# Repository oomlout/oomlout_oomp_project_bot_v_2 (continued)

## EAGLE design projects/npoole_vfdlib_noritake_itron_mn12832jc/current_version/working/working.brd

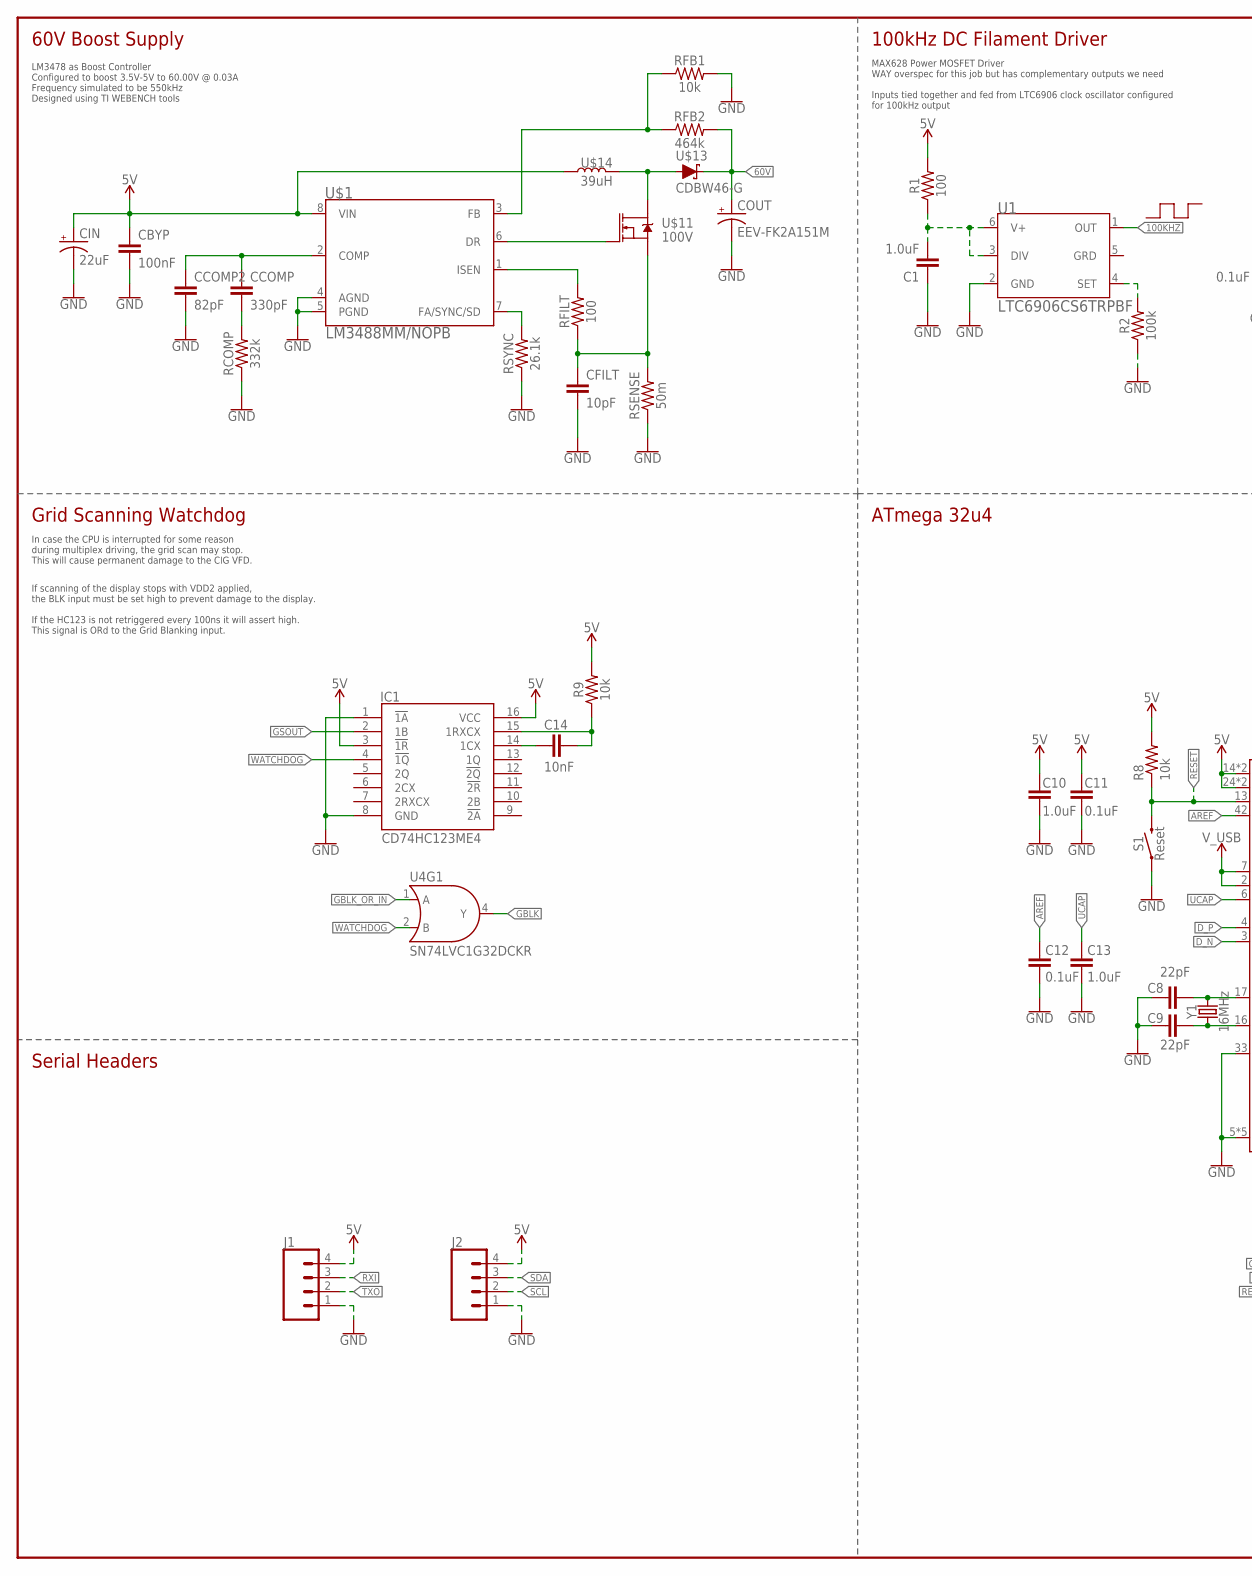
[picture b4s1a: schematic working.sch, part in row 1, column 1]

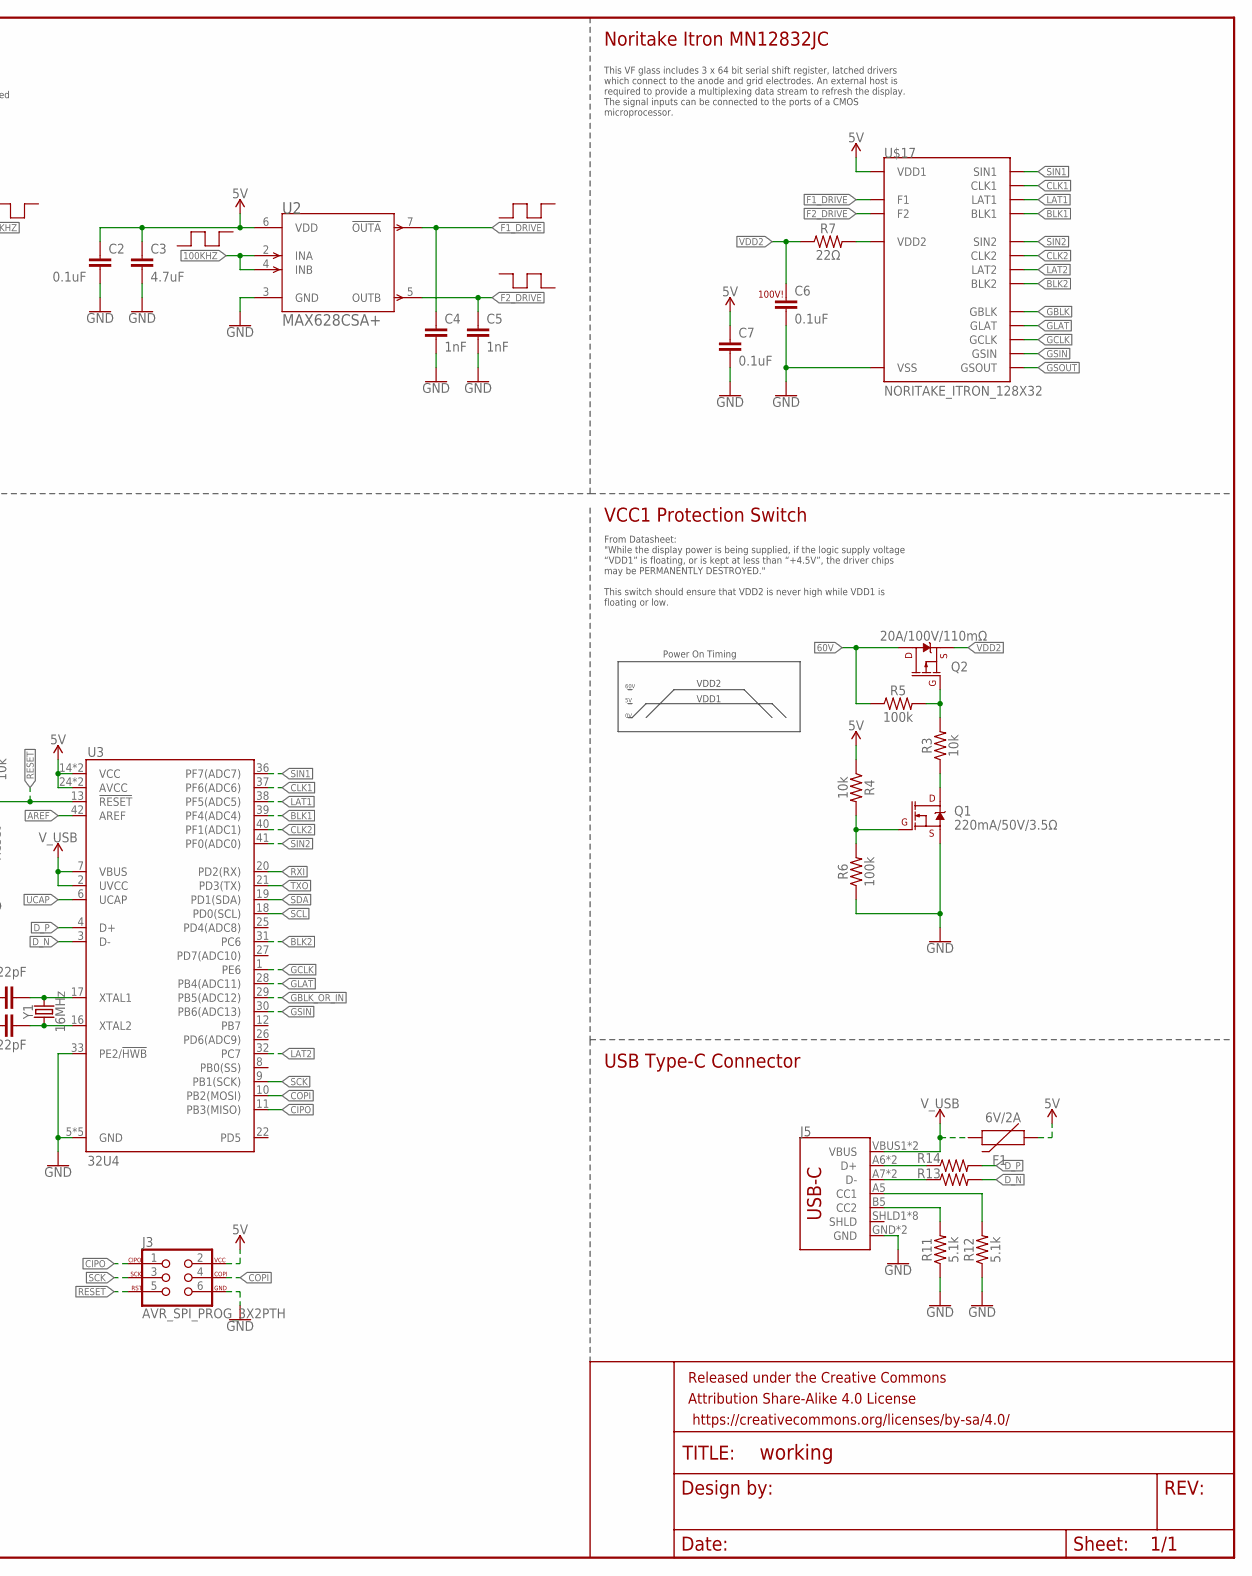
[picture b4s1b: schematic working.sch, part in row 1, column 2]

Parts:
C1, C10, C13: 1.0uF; 0603
C2, C6, C7, C11, C12: 0.1uF; 0603
C3: 4.7uF; 0603
C4, C5: 1nF; 0603
C8, C9: 22pF; 0603
C14: 10nF; 0603
CBYP: 100nF; 0805
CCOMP: 330pF; 0805
CCOMP2: 82pF; 0805
CFILT: 10pF; 0603
CIN: 22uF; SM_RADIAL_C
COUT: EEV-FK2A151M; SM_RADIAL_J16
F1: 6V/2A; 1210
FRAME1: FRAME-LEDGERNO_FOOTPRINT; DUMMY
IC1: CD74HC123ME4; SOIC127P600X175-16N
J1, J2: CONN_041X04_NO_SILK; 1X04_NO_SILK
J3: AVR_SPI_PROG_3X2PTH; 2X3
J5: USB_C5; USB-C-16P-5
Q1: 220mA/50V/3.5Ω; SOT23-3
Q2: 20A/100V/110mΩ; TO-252/DPAK
R1: 100; 0603
R2, R5, R6: 100k; 0603
R3, R4, R8, R9: 10k; 0603
R7, R13, R14: 22Ω; 0603
R11, R12: 5.1k; 0603
RCOMP: 332k; 0603
RFB1: 10k; 0603
RFB2: 464k; 0603
RFILT: 100; 0603
RSENSE: 50m; 0603
RSYNC: 26.1k; 0603
S1: Reset; TACTILE_SWITCH_SMD_4.6X2.8MM
U1: LTC6906CS6TRPBF; TSOT-23_6_ADI
U2: MAX628CSA+; 21-0041B_8_MXM
U3: 32U4; TQFP44
U4: SN74LVC1G32DCKR; SOT353
U$1: LM3488MM/NOPB; MUA08A
U$11: 100V; PG-TDSON-8
U$13: CDBW46-G; SOD-123
U$14: 39uH; IND_NPI54C
U$17: NORITAKE_ITRON_128X32
Y1: 16MHz; CRYSTAL-SMD-5X3.2-4PAD

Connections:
5V: C2.1, C3.1, C7.1, C10.2, C11.2, CBYP.1, CIN.1 (+), F1.1, IC1.3 (!1R), IC1.16 (VCC), J1.4, J2.4, J3.2, R1.2, R4.1, R8.2, R9.2, U2.6 (VDD), U3.14 (VCC), U3.24 (AVCC), U3.34 (VCC), U3.44 (AVCC), U$1.8 (VIN), U$14.1, U$17.P$13 (VDD1)
60V: COUT.1 (+), Q2.2 (D), R5.1, RFB2.2, U$13.1 (C)
100KHZ: U1.1 (OUT), U2.2 (INA), U2.4 (INB)
AREF: C12.2, U3.42 (AREF)
BLK1: U3.39 (PF4(ADC4)), U$17.P$4 (BLK1)
BLK2: U3.31 (PC6), U$17.P$23 (BLK2)
CIPO: J3.1, U3.11 (PB3(MISO))
CLK1: U3.37 (PF6(ADC6)), U$17.P$6 (CLK1)
CLK2: U3.40 (PF1(ADC1)), U$17.P$21 (CLK2)
COPI: J3.4, U3.10 (PB2(MOSI))
D-_HV: J5.A7 (D-), J5.B7 (D-), R13.1
DP_HV: J5.A6 (D+), J5.B6 (D+), R14.1
D_N: R13.2, U3.3 (D-)
D_P: R14.2, U3.4 (D+)
F1_DRIVE: C4.1, U2.7 (!OUTA), U$17.P$1 (F1), U$17.P$2 (F1), U$17.P$3 (F1)
F2_DRIVE: C5.1, U2.5 (OUTB), U$17.P$26 (F2), U$17.P$27 (F2), U$17.P$28 (F2)
GBLK: U4.4 (Y), U$17.P$14 (GBLK)
GBLK_OR_IN: U3.29 (PB5(ADC12)), U4.1 (A)
GCLK: U3.1 (PE6), U$17.P$16 (GCLK)
GLAT: U3.28 (PB4(ADC11)), U$17.P$15 (GLAT)
GND: C1.1, C2.2, C3.2, C4.2, C5.2, C6.2, C7.2, C8.2, C9.2, C10.1, C11.1, C12.1, C13.1, CBYP.2, CCOMP2.2, CFILT.2, CIN.2 (-), COUT.2 (-), IC1.1 (!1A), IC1.8 (GND), J1.1, J2.1, J3.6, J5.GND, J5.GND2 (GND), Q1.2 (S), R2.1, R6.1, R11.1, R12.1, RCOMP.1, RFB1.2, RSENSE.1, RSYNC.1, S1.1, S1.2 (1), U1.2 (GND), U2.3 (GND), U3.5 (GND), U3.15 (GND), U3.23 (GND), U3.33 (PE2/!HWB), U3.35 (GND), U3.43 (GND), U$1.4 (AGND), U$1.5 (PGND), U$17.P$11 (VSS), U$17.P$12 (VSS)
GSIN: U3.30 (PB6(ADC13)), U$17.P$17 (GSIN)
GSOUT: IC1.2 (1B), U$17.P$18 (GSOUT)
LAT1: U3.38 (PF5(ADC5)), U$17.P$5 (LAT1)
LAT2: U3.32 (PC7), U$17.P$22 (LAT2)
unnamed: RSYNC.2, U$1.7 (FA/SYNC/SD)
unnamed: CCOMP.1, CCOMP2.1, U$1.2 (COMP)
unnamed: RFILT.2, U$1.1 (ISEN)
unnamed: CCOMP.2, RCOMP.2
unnamed: CFILT.1, RFILT.1, RSENSE.2, U$11.1 (S), U$11.2 (S), U$11.3 (S)
unnamed: U$11.5 (D), U$11.6 (D), U$11.7 (D), U$11.8 (D), U$11.9 (D), U$13.2 (A), U$14.2
unnamed: RFB1.1, RFB2.1, U$1.3 (FB)
unnamed: U$1.6 (DR), U$11.4 (G)
unnamed: C1.2, R1.1, U1.3 (DIV), U1.6 (V+)
unnamed: R2.2, U1.4 (SET)
unnamed: R7.2, U$17.P$9 (VDD2), U$17.P$10 (VDD2)
unnamed: Q1.1 (G), R4.2, R6.2
unnamed: Q1.3 (D), R3.1
unnamed: Q2.1 (G), R3.2, R5.2
unnamed: C9.1, U3.16 (XTAL2), Y1.1
unnamed: C8.1, U3.17 (XTAL1), Y1.3 (2)
unnamed: C14.2, IC1.14 (1CX)
unnamed: C14.1, IC1.15 (1RXCX), R9.1
unnamed: J5.A5 (CC1), R12.2
unnamed: J5.B5 (CC2), R11.2
RESET: J3.5, R8.1, S1.3 (2), S1.4 (2), U3.13 (!RESET)
RXI: J1.3, U3.20 (PD2(RX))
SCK: J3.3, U3.9 (PB1(SCK))
SCL: J2.2, U3.18 (PD0(SCL))
SDA: J2.3, U3.19 (PD1(SDA))
SIN1: U3.36 (PF7(ADC7)), U$17.P$7 (SIN1)
SIN2: U3.41 (PF0(ADC0)), U$17.P$20 (SIN2)
TXO: J1.2, U3.21 (PD3(TX))
UCAP: C13.2, U3.6 (UCAP)
VDD2: C6.1, Q2.3 (S), R7.1
V_USB: F1.2, J5.VBUS1 (VBUS), J5.VBUS2 (VBUS), U3.2 (UVCC), U3.7 (VBUS)
WATCHDOG: IC1.4 (!1Q), U4.2 (B)

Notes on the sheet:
60V Boost Supply
100kHz DC Filament Driver
100V!
Noritake Itron MN12832JC
VCC1 Protection Switch
LM3478 as Boost Controller Configured to boost 3.5V-5V to 60.00V @ 0.03A Frequency simulated to be 550kHz Designed using TI WEBENCH tools
MAX628 Power MOSFET Driver WAY overspec for this job but has complementary outputs we need Inputs tied together and fed from LTC6906 clock oscillator configured for 100kHz output
From Datasheet: "While the display power is being supplied, if the logic supply voltage “VDD1” is floating, or is kept at less than “+4.5V”, the driver chips may be PERMANENTLY DESTROYED." This switch should ensure that VDD2 is never high while VDD1 is floating or low.
VDD1
VDD2
60V
Power On Timing
This VF glass includes 3 x 64 bit serial shift register, latched drivers which connect to the anode and grid electrodes. An external host is required to provide a multiplexing data stream to refresh the display. The signal inputs can be connected to the ports of a CMOS microprocessor.
ATmega 32u4
USB Type-C Connector
Grid Scanning Watchdog
In case the CPU is interrupted for some reason during multiplex driving, the grid scan may stop. This will cause permanent damage to the CIG VFD.
If scanning of the display stops with VDD2 applied, the BLK input must be set high to prevent damage to the display. If the HC123 is not retriggered every 100ns it will assert high. This signal is ORd to the Grid Blanking input.
Serial Headers

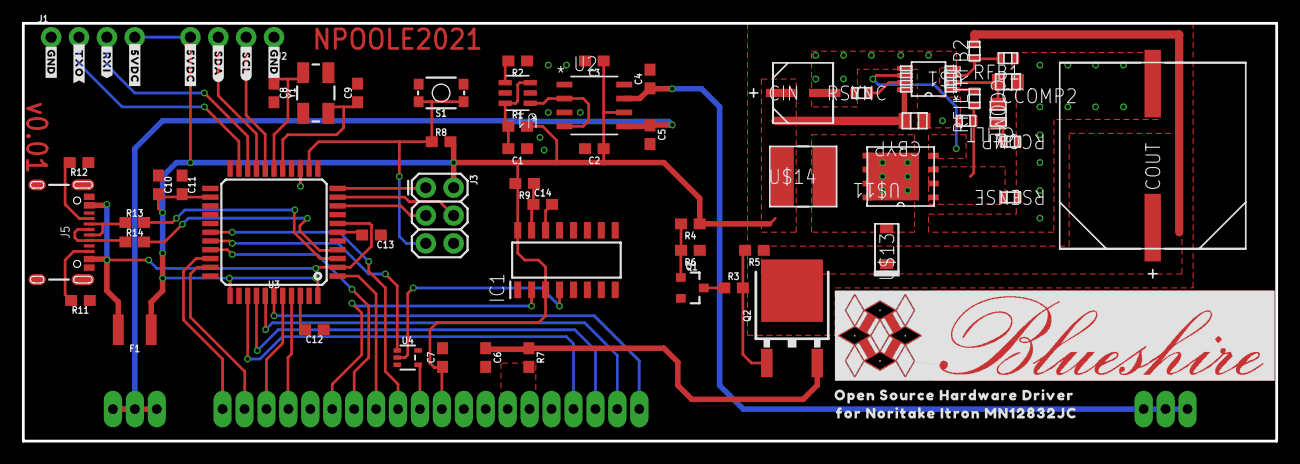
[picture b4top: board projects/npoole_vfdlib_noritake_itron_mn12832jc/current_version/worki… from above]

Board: 2 copper layers, 114.3 x 38.1 mm, 72 parts (1 on the bottom side), 57 nets.

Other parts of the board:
U$2: BLUESHIRE_COPPER#SVG1
U$3: BLUESHIRE_SILK#SVG0
U$4: BLUESHIRE_STOP#SVG2
U$5: OPEN_SOURCE_HARDWARE_DRIVER0
U$6: FOR_NORITAKE_ITRON_MN12832JC0
U$7, U$15: #GND#0
U$8: #_SCL#0
U$9: #_SDA#0
U$10, U$12: #_5VDC#0
U$16: #_RXI#0
U$18: #_TXO#0

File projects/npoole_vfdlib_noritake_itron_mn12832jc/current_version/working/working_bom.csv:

"Id";"Designator";"Footprint";"Quantity";"Designation";"Supplier and ref";
1;"U$18";"#_TXO#0";1;"";;;
2;"CCOMP0";"0805";1;"330pF";;;
3;"R7,R14,R13";"0603";3;"22Ω";;;
4;"F1";"1210";1;"6V/2A";;;
5;"C8,C9";"0603";2;"22pF";;;
6;"COUT0";"SM_RADIAL_J16";1;"EEV-FK2A151M";;;
7;"C12,C6,C7,C2,C11";"0603";5;"0.1uF";;;
8;"U$15,U$7";"#GND#0";2;"";;;
9;"U2";"21-0041B_8_MXM";1;"MAX628CSA+";;;
10;"C4,C5";"0603";2;"1nF";;;
11;"IC1";"SOIC127P600X175-16N";1;"CD74HC123ME4";;;
12;"J1,J2";"1X04_NO_SILK";2;"";;;
13;"U$3";"BLUESHIRE_SILK#SVG0";1;"";;;
14;"S1";"TACTILE_SWITCH_SMD_4.6X2.8MM";1;"Reset";;;
15;"U$16";"#_RXI#0";1;"";;;
16;"R6,R2,R5";"0603";3;"100k";;;
17;"U$10,U$12";"#_5VDC#0";2;"";;;
18;"U$8";"#_SCL#0";1;"";;;
19;"CCOMP2";"0805";1;"82pF";;;
20;"Q1";"SOT23-3";1;"220mA/50V/3.5Ω";;;
21;"CBYP0";"0805";1;"100nF";;;
22;"U$14";"IND_NPI54C";1;"39uH";;;
23;"R3,R8,RFB1,R9,R4";"0603";5;"10k";;;
24;"U$6";"FOR_NORITAKE_ITRON_MN12832JC0";1;"";;;
25;"J3";"2X3";1;"AVR_SPI_PROG_3X2PTH";;;
26;"C3";"0603";1;"4.7uF";;;
27;"RCOMP0";"0603";1;"332k";;;
28;"RFILT0,R1";"0603";2;"100";;;
29;"U$11";"PG-TDSON-8";1;"100V";;;
30;"FRAME1";"DUMMY";1;"FRAME-LEDGERNO_FOOTPRINT";;;
31;"U$5";"OPEN_SOURCE_HARDWARE_DRIVER0";1;"";;;
32;"U1";"TSOT-23_6_ADI";1;"LTC6906CS6TRPBF";;;
33;"Q2";"TO-252_DPAK";1;"20A/100V/110mΩ";;;
34;"RSYNC0";"0603";1;"26.1k";;;
35;"CFILT0";"0603";1;"10pF";;;
36;"Y1";"CRYSTAL-SMD-5X3.2-4PAD";1;"16MHz";;;
37;"U$4";"BLUESHIRE_STOP#SVG2";1;"";;;
38;"CIN0";"SM_RADIAL_C";1;"22uF";;;
39;"RSENSE0";"0603";1;"50m";;;
40;"U3";"TQFP44";1;"32U4";;;
41;"R11,R12";"0603";2;"5.1k";;;
42;"U4";"SOT353";1;"SN74LVC1G32DCKR";;;
43;"U$9";"#_SDA#0";1;"";;;
44;"U$13";"SOD-123";1;"CDBW46-G";;;
45;"C10,C13,C1";"0603";3;"1.0uF";;;
46;"C14";"0603";1;"10nF";;;
47;"RFB2";"0603";1;"464k";;;
48;"U$2";"BLUESHIRE_COPPER#SVG1";1;"";;;
49;"U$1";"MUA08A";1;"LM3488MM/NOPB";;;
50;"J5";"USB-C-16P-5";1;"";;;
51;"U$17";"NORITAKE_ITRON_128X32";1;"NORITAKE_ITRON_128X32";;;

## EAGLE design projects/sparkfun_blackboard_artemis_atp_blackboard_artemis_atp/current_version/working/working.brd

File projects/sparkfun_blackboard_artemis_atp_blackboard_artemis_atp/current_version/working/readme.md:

# blackboard_artemis_atp
 
## summary 
* id: sparkfun_blackboard_artemis_atp_blackboard_artemis_atp
* user: sparkfun
* name: blackboard_artemis_atp
* board: blackboard_artemis_atp
* repo: https://github.com/sparkfun/BlackBoard_Artemis_ATP

* src_file_repo_sch: 
* src_file_repo_sch_link: https://github.com/sparkfun/BlackBoard_Artemis_ATP/tree/master/
* full details link: https://github.com/oomlout/oomlout_oomp_project_bot_v_2/tree/main/projects/sparkfun_blackboard_artemis_atp_blackboard_artemis_atp/current_version/working

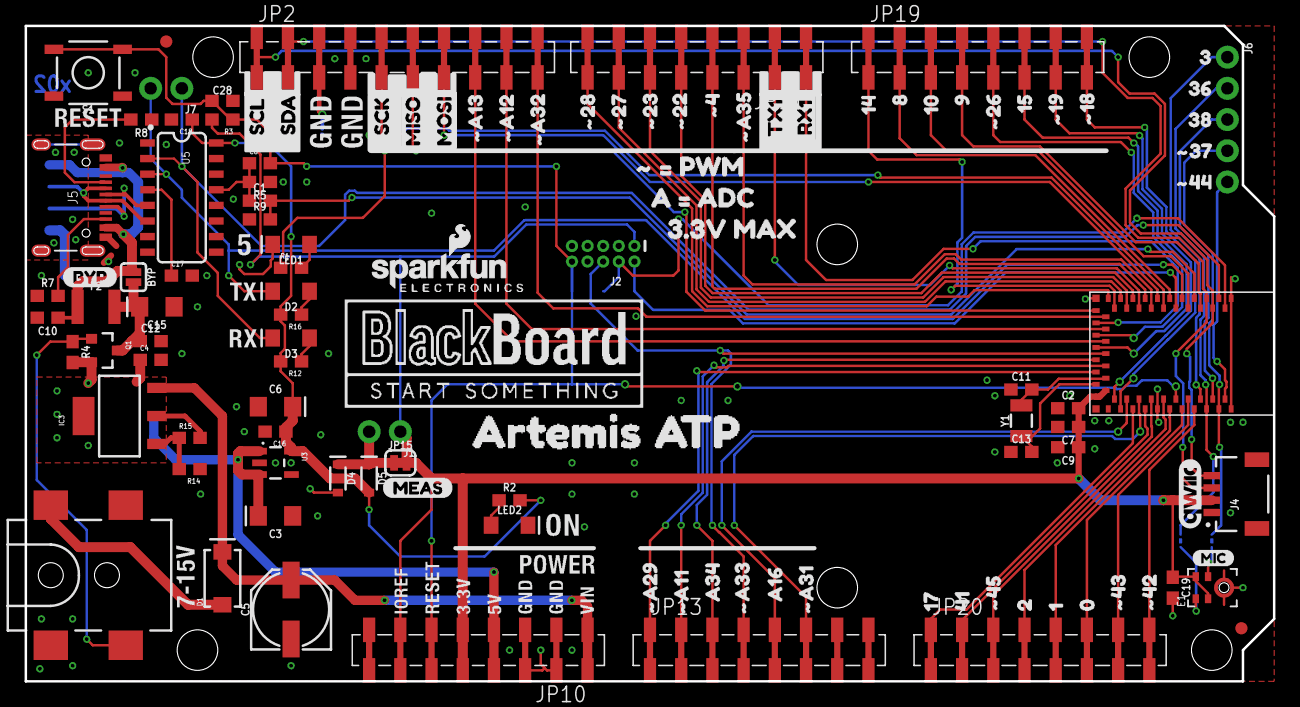
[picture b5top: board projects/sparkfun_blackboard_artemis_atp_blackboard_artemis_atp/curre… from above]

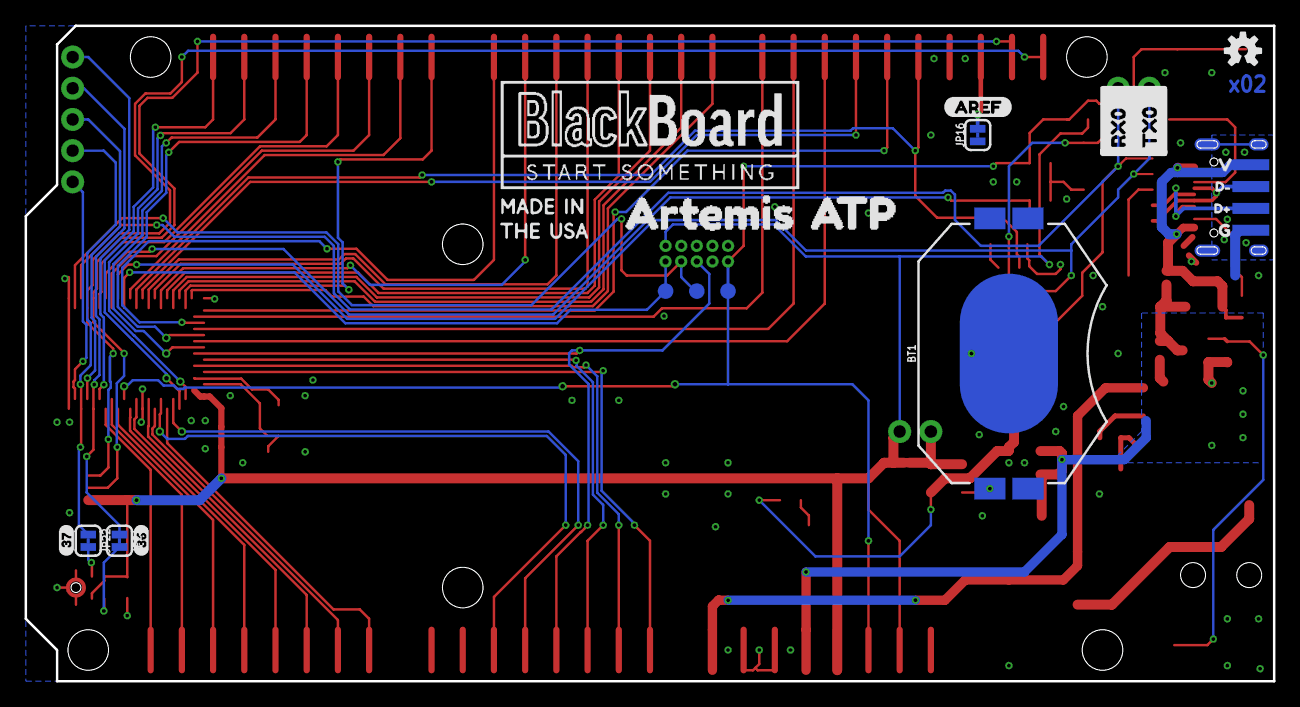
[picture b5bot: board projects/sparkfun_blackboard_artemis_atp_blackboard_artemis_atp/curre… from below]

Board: 2 copper layers, 101.6 x 53.3 mm, 149 parts (23 on the bottom side), 77 nets.

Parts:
BT1: CR2032; BATTCON_20MM_4LEGS_OVERPASTE
BYP: BYP; SMT-JUMPER_2_NO_SILK
C1: 2.2uF; 0603
C2, C4, C8, C10, C12, C18, C19: 0.1uF; 0603
C3, C6, C15: 10uF; EIA3216
C5: 47uF; PANASONIC_D
C7: 10uF; 0603
C9, C16: 1.0uF; 0603
C11, C13: 15pF; 0603
C17: 10nF; 0603
C28: 1nF; 0603
D1: 1A/40V/500mV; SMA-DIODE
D2: GREEN; LED-1206
D3: Yellow; LED-1206
D4, D5: 1A/23V/620mV; SOD-323
E1: SPH0641LM4H-1; SPH0641LM4H-1_MICROPHONE
F2: 6V/2A; 1210
FRAME1: FRAME-LETTER; CREATIVE_COMMONS
FRAME2: FRAME-LETTERNO_PACKAGE; DUMMY
IC3: LM1117; SOT223-ALT1
J1, J7: 1X02_NO_SILK
J2: CORTEX_DEBUG; 2X5-PTH-1.27MM-NO_SILK
J3: POWER_JACKTOE; POWER_JACK_SMD_OVERPASTE_TOE
J4: JST04_1MM_RA
J5: USB-C; USB-C-16P
J6: 1X05_NO_SILK
JP1: SFE_LOGO_NAME.1_INCH; SFE_LOGO_NAME_.1
JP2: M10SMD_COMBO; 1X10_SMD_COMBINED
JP3, JP4, JP5, JP6, JP17, JP18: STAND-OFF
JP7: SFE_LOGO_FLAME.1_INCH; SFE_LOGO_FLAME_.1
JP8, JP9: FIDUCIAL1X2; FIDUCIAL-1X2
JP10: 1X08_SMD_COMBINED
JP11, JP13, JP19, JP20: JP11; 1X08_SMD_COMBINED
JP14: USB_SOLDER_PADS; USB-SOLDER-PADS
JP15, JP16, JP21, JP22: SMT-JUMPER_2_NC_TRACE_SILK
LED1: BLUE; LED-1206
LED2: GREEN; LED-1206
Q1: 1.1A/60V/600mΩ; SOT23-3
R1, R12, R16: 4.7k; 0603
R2, R4, R9: 10k; 0603
R3, R5: 100k; 0603
R7, R8: 5.1k; 0603
R14: 715; 0603
R15: 240; 0603
S1: TACTILE_SWITCH_SMD_5.2MM
TP1, TP2, TP3: PAD.03X.05
U3: AP2112-3.3V; SOT23-5
U4: ARTEMIS_MODULESMD; ARTEMIS_FP
U5: CH340C; SO016
U$1, U$3: BLACKBOARDLOGO#PNG
U$2: D#3
U$4: MADEINUSA#PNG
U$9: QWIIC_COPYRIGHT_SMALL
U$10: D#4
U$11: G1
U$12: V0
U$13: #A332
U$14, U$15: ARTEMIS0
U$16: OSHW-LOGOS; OSHW-LOGO-S
U$17: A160
U$18: SCL1
U$19: #48
U$20: AREF2
U$21: #229
U$22: SDA0
U$23: #3711
U$24: #187
U$25: #2310
U$26: #2711
U$27: #2812
U$28, U$61: ATP1
U$29: #A113
U$30: #A294
U$31: #A310
U$32: #196
U$33: #A357
U$34: #A1214
U$35: #A1315
U$36: #A3213
U$37: #264
U$38: A342
U$39: #4213
U$40: #4314
U$41: #4412
U$42: #4518
U$43: 015
U$44: 38
U$45: 81
U$46: 93
U$47: MISO8
U$48: MOSI7
U$49: RX01
U$50: SCK9
U$51: 102
U$52: 116
U$53: TX00
U$54: 140
U$55: 155
U$56: 217
U$57: 369
U$58: 1720
U$59: 3810
U$60: 4119
U$62: MIC0
U$63: 364
U$64: 373
U$66: #_#_PWM7
U$67: 3#3V_MAX2
U$68: BYP0
U$69: A_#_ADC6
U$70: MEAS3
U$71: RX11
U$72: TX10
Y1: 32.768kHz; CRYSTAL-SMD-3.2X1.5MM

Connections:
3.3V: C6.+, C16.1, C18.1, D5.A, R2.2, R12.2, R16.2, U3.5, U5.16
5V: C3.+, C4.1, IC3.2, IC3.4, JP10.4A, JP10.4B, Q1.2, R4.2, R15.2, U3.1, U3.3
!DTR: C1.1, C8.1, R5.2, U5.13
!RESET: C8.2, C28.1, J2.10, JP10.6A, JP10.6B, R3.1, S1.3, S1.4, TP3.P$1, U4.~RST
AD16: JP13.5A, JP13.5B, U4.AD16
AD34: JP13.3A, JP13.3B, U4.AD34
BOOT: C1.2, R9.2, U4.BOOT
CC1: J5.A5, R8.2
CC2: J5.B5, R7.2
D0: JP20.6A, JP20.6B, U4.D0
D1: JP20.5A, JP20.5B, U4.D1
D2: JP20.4A, JP20.4B, U4.D2
D3: J6.1, U4.D3
D8: JP19.2A, JP19.2B, U4.D8
D9: JP19.4A, JP19.4B, U4.D9
D10: JP19.3A, JP19.3B, U4.D10
D14: JP19.1A, JP19.1B, U4.D14
D15: JP19.6A, JP19.6B, U4.D15
D17: JP20.1A, JP20.1B, U4.D17
D36: J6.2, JP21.1, U4.D36
D38: J6.3, U4.D38
D40/SDA: J4.3, JP2.2A, JP2.2B, U4.D40
D41: JP20.2A, JP20.2B, U4.D41
D+: J5.A6, J5.B6, JP14.D+, U5.5
D-: J5.A7, J5.B7, JP14.D-, U5.6
GND: BT1.2, C2.1, C3.-, C4.2, C5.-, C6.-, C7.2, C9.2, C10.2, C11.1, C12.2, C13.1, C15.-, C16.2, C17.2, C18.2, C19.2, C28.2, E1.3, E1.6, E1.7, E1.8, J2.3, J2.5, J2.9, J3.GND, J4.1, J5.GND, J5.GND2, JP2.4A, JP2.4B, JP10.2A, JP10.2B, JP10.3A, JP10.3B, JP14.GND, JP16.1, LED1.C, LED2.C, R5.1, R7.1, R8.1, R9.1, R14.1, S1.1, S1.2, U3.2, U4.GND@1, U4.GND@22, U4.GND@38, U4.GND@39, U4.GND@47, U4.GND@59, U5.1
INSERT: J3.P$4, Q1.1, R4.1
unnamed: LED1.A, R1.2
unnamed: LED2.A, R2.1
unnamed: D4.C, D5.C, J1.2, JP15.1
unnamed: D2.A, R16.1
unnamed: C17.1, U5.4
unnamed: C11.2, U4.XO, Y1.P$2
unnamed: C13.2, U4.XI, Y1.P$1
unnamed: D3.A, R12.1
unnamed: JP2.3A, JP2.3B, JP16.2
unnamed: IC3.1, R14.2, R15.1
PDMCLK: E1.4, JP22.2
PDMDATA: E1.1, JP21.2
PWRIN: D1.A, J3.VIN0
RXI-0: D3.C, J7.1, U4.RXI-0, U5.2
SHLD: J5.SHLD1, J5.SHLD2, J5.SHLD3, J5.SHLD4, J5.SHLD5, J5.SHLD6, J5.SHLD7, J5.SHLD8
SWDCK: J2.4, TP1.P$1, U4.SWDCK
SWDIO: J2.2, TP2.P$1, U4.SWDIO
TXO-0: D2.C, J7.2, U4.TXO-0, U5.3
USBVCC: BYP.2, C12.1, C15.+, F2.2, Q1.3
VDD: C2.2, C7.1, C9.1, C19.1, E1.2, E1.5, J1.1, J2.1, J4.2, JP10.5A, JP10.5B, JP10.7A, JP10.7B, JP15.2, R3.2, U4.VDD@36, U4.VDD@37
VIN: C5.+, D1.C, IC3.3, JP10.1A, JP10.1B
VUSB: BYP.1, C10.1, F2.1, J5.VBUS1, J5.VBUS2, JP14.VBUS
V_BATT: BT1.1, D4.A
~AD11: JP13.2A, JP13.2B, U4.~AD11
~AD12: JP2.9A, JP2.9B, U4.~AD12
~AD13: JP2.8A, JP2.8B, U4.~AD13
~AD29: JP13.1A, JP13.1B, U4.~AD29
~AD31: JP13.6A, JP13.6B, U4.~AD31
~AD32: JP2.10A, JP2.10B, U4.~AD32
~AD33/SWO: J2.6, JP13.4A, JP13.4B, U4.~AD33/SWO
~AD35: JP11.3A, JP11.3B, U4.~AD35
~D4: JP11.4A, JP11.4B, U4.~D4
~D5/SCK: JP2.5A, JP2.5B, R1.1, U4.~D5
~D6/MISO: JP2.6A, JP2.6B, U4.~D6
~D7/MOSI: JP2.7A, JP2.7B, U4.D7
~D18: JP19.8A, JP19.8B, U4.~D18
~D19: JP19.7A, JP19.7B, U4.~D19
~D22: JP11.5A, JP11.5B, U4.~D22
~D23: JP11.6A, JP11.6B, U4.~D23
~D24/TXO-1: JP11.2A, JP11.2B, U4.~D24
~D25/RXI-1: JP11.1A, JP11.1B, U4.~D25
~D26: JP19.5A, JP19.5B, U4.~D26
~D27: JP11.7A, JP11.7B, U4.~D27
~D28: JP11.8A, JP11.8B, U4.~D28
~D37: J6.4, JP22.1, U4.~D37
~D39/SCL: J4.4, JP2.1A, JP2.1B, U4.~D39
~D42: JP20.8A, JP20.8B, U4.~D42
~D43: JP20.7A, JP20.7B, U4.~D43
~D44: J6.5, U4.~D44
~D45: JP20.3A, JP20.3B, U4.~D45

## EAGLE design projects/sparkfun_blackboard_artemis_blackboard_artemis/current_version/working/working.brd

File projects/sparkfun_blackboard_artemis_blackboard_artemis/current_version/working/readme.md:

# blackboard_artemis
 
## summary 
* id: sparkfun_blackboard_artemis_blackboard_artemis
* user: sparkfun
* name: blackboard_artemis
* board: blackboard_artemis
* repo: https://github.com/sparkfun/BlackBoard_Artemis

* src_file_repo_sch: 
* src_file_repo_sch_link: https://github.com/sparkfun/BlackBoard_Artemis/tree/master/
* full details link: https://github.com/oomlout/oomlout_oomp_project_bot_v_2/tree/main/projects/sparkfun_blackboard_artemis_blackboard_artemis/current_version/working

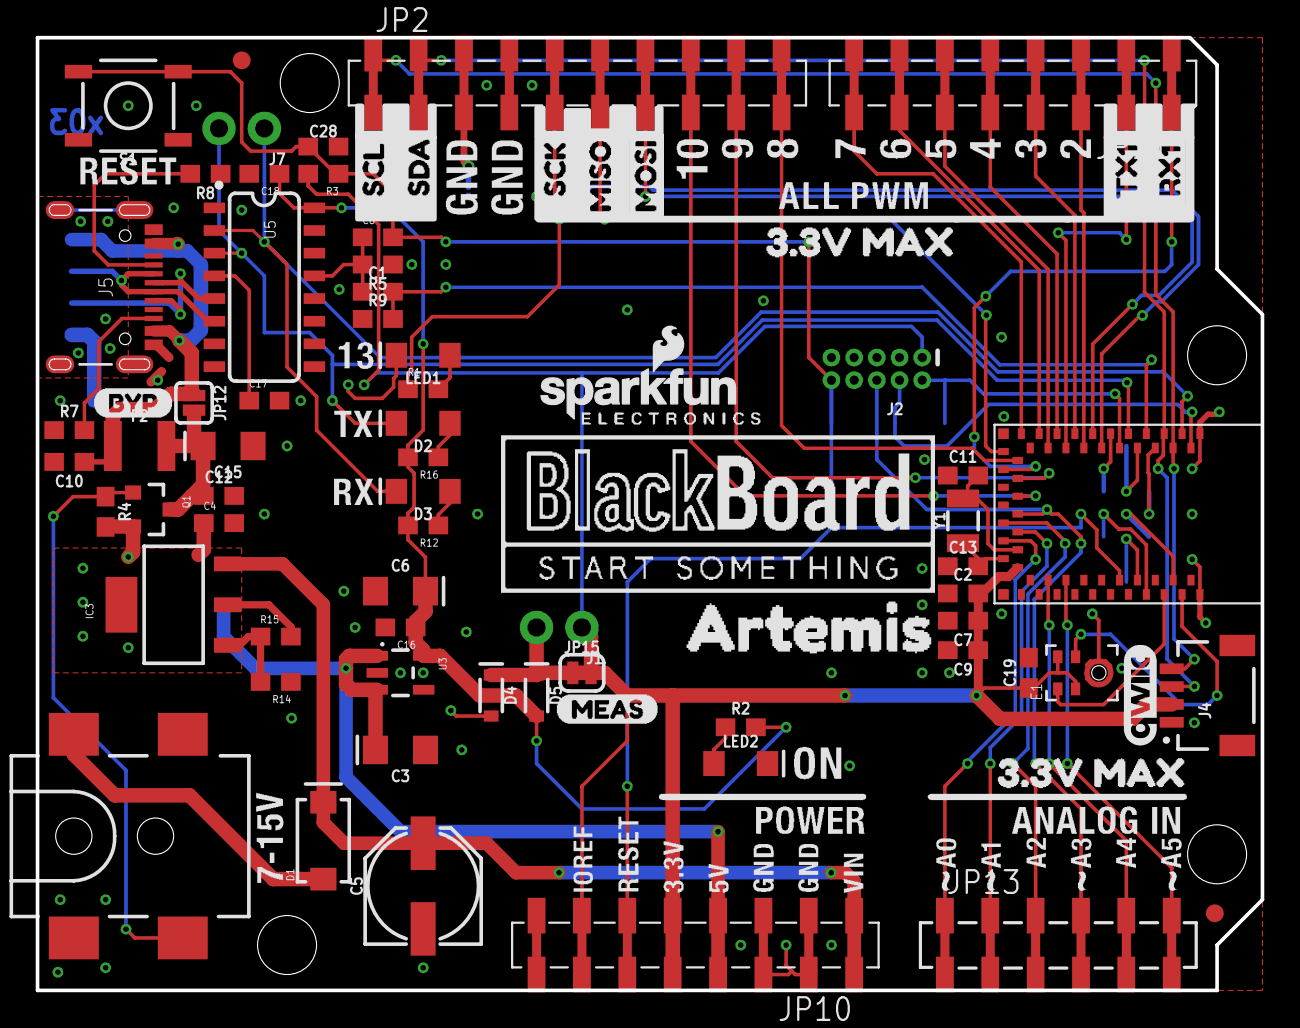
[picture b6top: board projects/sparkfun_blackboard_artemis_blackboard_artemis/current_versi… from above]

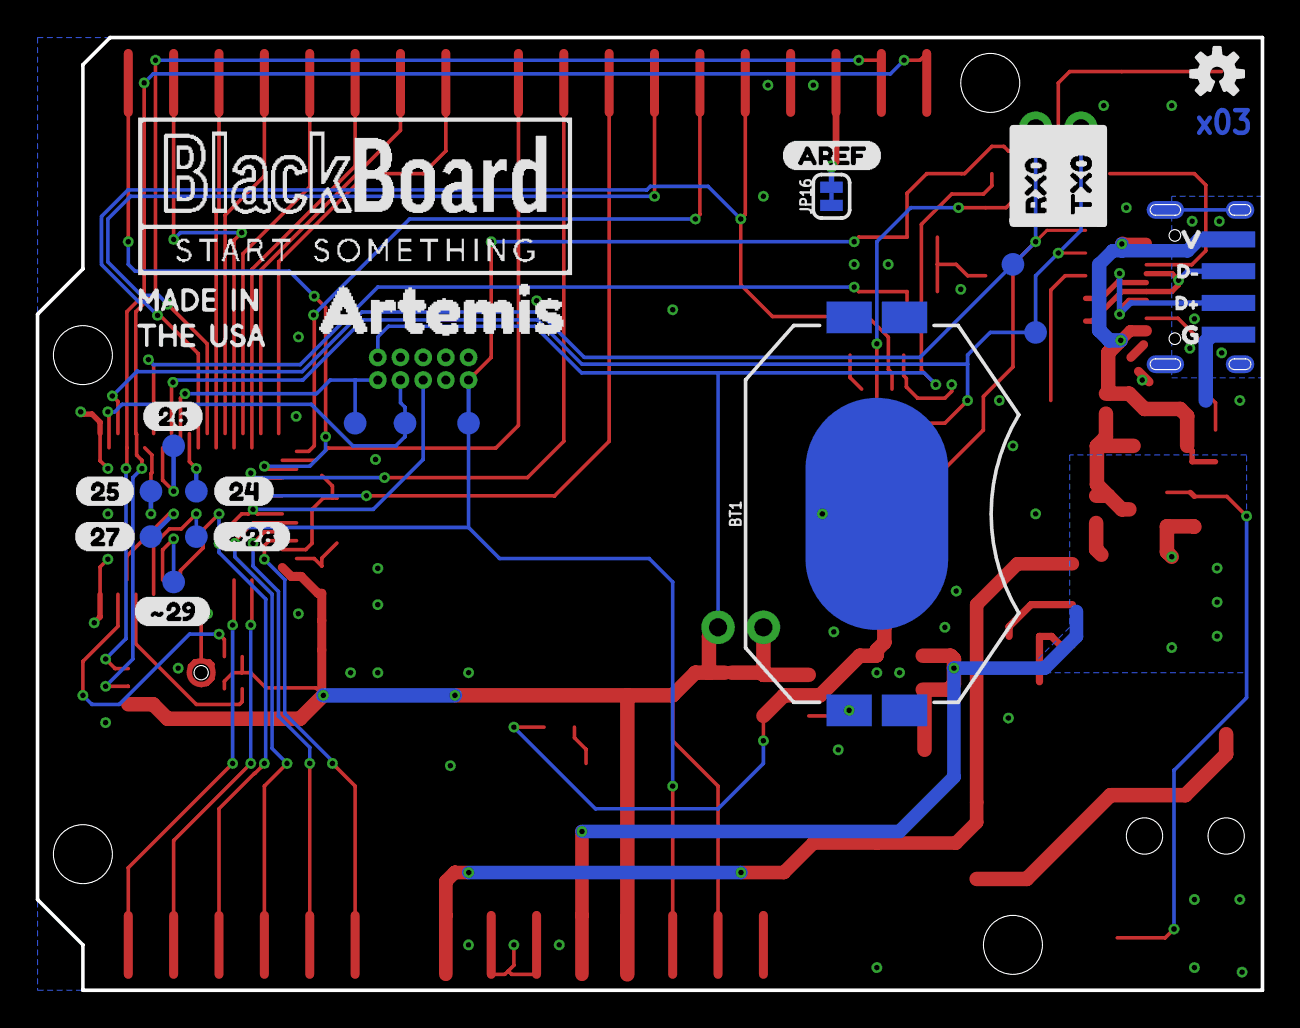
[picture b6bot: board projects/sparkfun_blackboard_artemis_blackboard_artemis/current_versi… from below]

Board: 2 copper layers, 68.6 x 53.3 mm, 114 parts (32 on the bottom side), 62 nets.

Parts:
BT1: CR2032; BATTCON_20MM_4LEGS_OVERPASTE
C1: 2.2uF; 0603
C2, C4, C8, C10, C12, C18, C19: 0.1uF; 0603
C3, C6, C15: 10uF; EIA3216
C5: 47uF; PANASONIC_D
C7: 10uF; 0603
C9, C16: 1.0uF; 0603
C11, C13: 15pF; 0603
C17: 10nF; 0603
C28: 1nF; 0603
D1: 1A/40V/500mV; SMA-DIODE
D2: GREEN; LED-1206
D3: Yellow; LED-1206
D4, D5: 1A/23V/620mV; SOD-323
E1: SPH0641LM4H-1; SPH0641LM4H-1_MICROPHONE
F2: 6V/2A; 1210
FRAME1: FRAME-LETTER; CREATIVE_COMMONS
FRAME2: FRAME-LETTERNO_PACKAGE; DUMMY
IC3: LM1117; SOT223-ALT1
J1, J7: 1X02_NO_SILK
J2: CORTEX_DEBUG; 2X5-PTH-1.27MM-NO_SILK
J3: POWER_JACKTOE; POWER_JACK_SMD_OVERPASTE_TOE
J4: JST04_1MM_RA
J5: USB-C; USB-C-16P
JP1: SFE_LOGO_NAME.1_INCH; SFE_LOGO_NAME_.1
JP2: M10SMD_COMBO; 1X10_SMD_COMBINED
JP3, JP4, JP5, JP6: STAND-OFF
JP7: SFE_LOGO_FLAME.1_INCH; SFE_LOGO_FLAME_.1
JP8, JP9: FIDUCIAL1X2; FIDUCIAL-1X2
JP10: 1X08_SMD_COMBINED
JP11: JP11; 1X08_SMD_COMBINED
JP12: SMT-JUMPER_2_NO_SILK
JP13: 1X06_SMD_STRAIGHT_COMBO
JP14: USB_SOLDER_PADS; USB-SOLDER-PADS
JP15, JP16: SMT-JUMPER_2_NC_TRACE_SILK
LED1: BLUE; LED-1206
LED2: GREEN; LED-1206
Q1: 1.1A/60V/600mΩ; SOT23-3
R1, R12, R16: 4.7k; 0603
R2, R4, R9: 10k; 0603
R3, R5: 100k; 0603
R7, R8: 5.1k; 0603
R14: 715; 0603
R15: 240; 0603
S1: TACTILE_SWITCH_SMD_5.2MM
TP1, TP2, TP3, TP8, TP9, TP11, TP12, TP13, TP14: PAD.03X.05
TP5, TP6: TEST-POINT3X5; PAD.03X.05
U1: ARTEMIS_MODULESMD; ARTEMIS_FP
U3: AP2112-3.3V; SOT23-5
U5: CH340C; SO016
U$1, U$3: BLACKBOARDLOGO#PNG
U$2: D#3
U$4: MADEINUSA#PNG
U$9: QWIIC_COPYRIGHT_SMALL
U$10: D#4
U$11: G1
U$12: V0
U$13, U$67: 3#3V_MAX2
U$14, U$15: ARTEMIS0
U$16: OSHW-LOGOS; OSHW-LOGO-S
U$17: #284
U$18: SCL1
U$19: #295
U$20: AREF2
U$21: 240
U$22: SDA0
U$23: 251
U$24: 262
U$25: 273
U$47: MISO8
U$48: MOSI7
U$49: RX01
U$50: SCK9
U$53: TX00
U$68: BYP0
U$70: MEAS3
U$71: RX11
U$72: TX10
Y1: 32.768kHz; CRYSTAL-SMD-3.2X1.5MM

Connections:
3.3V: C6.+, C16.1, C18.1, D5.A, R2.2, R12.2, R16.2, U3.5, U5.16
5V: C3.+, C4.1, IC3.2, IC3.4, JP10.4A, JP10.4B, Q1.2, R4.2, R15.2, U3.1, U3.3
!DTR: C1.1, C8.1, R5.2, U5.13
!RESET: C8.2, C28.1, J2.10, JP10.6A, JP10.6B, R3.1, S1.3, S1.4, TP3.P$1, U1.~RST
BOOT: C1.2, R9.2, U1.BOOT
CC1: J5.A5, R8.2
CC2: J5.B5, R7.2
D14/SDA: J4.3, JP2.2A, JP2.2B, U1.D40
D18/A2: JP13.3A, JP13.3B, U1.AD34
D20/A4: JP13.5A, JP13.5B, U1.AD16
D24: TP12.P$1, U1.D8
D25: TP13.P$1, U1.D9
D26: TP14.P$1, U1.D10
D27: TP11.P$1, U1.D38
D+: J5.A6, J5.B6, JP14.D+, U5.5
D-: J5.A7, J5.B7, JP14.D-, U5.6
GND: BT1.2, C2.1, C3.-, C4.2, C5.-, C6.-, C7.2, C9.2, C10.2, C11.1, C12.2, C13.1, C15.-, C16.2, C17.2, C18.2, C19.2, C28.2, E1.3, E1.6, E1.7, E1.8, J2.3, J2.5, J2.9, J3.GND, J4.1, J5.GND, J5.GND2, JP2.4A, JP2.4B, JP10.2A, JP10.2B, JP10.3A, JP10.3B, JP14.GND, JP16.1, LED1.C, LED2.C, R5.1, R7.1, R8.1, R9.1, R14.1, S1.1, S1.2, U1.GND@1, U1.GND@22, U1.GND@38, U1.GND@39, U1.GND@47, U1.GND@59, U3.2, U5.1
INSERT: J3.P$4, Q1.1, R4.1
unnamed: LED1.A, R1.2
unnamed: LED2.A, R2.1
unnamed: D4.C, D5.C, J1.2, JP15.1
unnamed: D2.A, R16.1
unnamed: C17.1, U5.4
unnamed: C11.2, U1.XO, Y1.P$2
unnamed: C13.2, U1.XI, Y1.P$1
unnamed: D3.A, R12.1
unnamed: JP2.3A, JP2.3B, JP16.2
unnamed: IC3.1, R14.2, R15.1
PDMCLK: E1.4, U1.~D37
PDMDATA: E1.1, U1.D36
PWRIN: D1.A, J3.VIN0
RXI-0: D3.C, J7.1, TP5.P$1, U1.RXI-0, U5.2
SHLD: J5.SHLD1, J5.SHLD2, J5.SHLD3, J5.SHLD4, J5.SHLD5, J5.SHLD6, J5.SHLD7, J5.SHLD8
SWDCK: J2.4, TP1.P$1, U1.SWDCK
SWDIO: J2.2, TP2.P$1, U1.SWDIO
TXO-0: D2.C, J7.2, TP6.P$1, U1.TXO-0, U5.3
USBVCC: C12.1, C15.+, F2.2, JP12.2, Q1.3
VDD: C2.2, C7.1, C9.1, C19.1, E1.2, E1.5, J1.1, J2.1, J4.2, JP10.5A, JP10.5B, JP10.7A, JP10.7B, JP15.2, R3.2, U1.VDD@36, U1.VDD@37
VIN: C5.+, D1.C, IC3.3, JP10.1A, JP10.1B
VUSB: C10.1, F2.1, J5.VBUS1, J5.VBUS2, JP12.1, JP14.VBUS
V_BATT: BT1.1, D4.A
~D0/RXI-1: JP11.1A, JP11.1B, U1.~D25
~D1/TXO-1: JP11.2A, JP11.2B, U1.~D24
~D2/A6: JP11.3A, JP11.3B, U1.~AD35
~D3: JP11.4A, JP11.4B, U1.~D4
~D4: JP11.5A, JP11.5B, U1.~D22
~D5: JP11.6A, JP11.6B, U1.~D23
~D6: JP11.7A, JP11.7B, U1.~D27
~D7: JP11.8A, JP11.8B, U1.~D28
~D8/A8: JP2.10A, JP2.10B, U1.~AD32
~D9/A9: JP2.9A, JP2.9B, U1.~AD12
~D10/A10: JP2.8A, JP2.8B, U1.~AD13
~D11/MOSI: JP2.7A, JP2.7B, U1.D7
~D12/MISO: JP2.6A, JP2.6B, U1.~D6
~D13/SCK: JP2.5A, JP2.5B, R1.1, U1.~D5
~D15/SCL: J4.4, JP2.1A, JP2.1B, U1.~D39
~D16/A0: JP13.1A, JP13.1B, U1.~AD29
~D17/A1: JP13.2A, JP13.2B, U1.~AD11
~D19/A3: J2.6, JP13.4A, JP13.4B, U1.~AD33/SWO
~D21/A5: JP13.6A, JP13.6B, U1.~AD31
~D28: TP9.P$1, U1.~D42
~D29: TP8.P$1, U1.~D43

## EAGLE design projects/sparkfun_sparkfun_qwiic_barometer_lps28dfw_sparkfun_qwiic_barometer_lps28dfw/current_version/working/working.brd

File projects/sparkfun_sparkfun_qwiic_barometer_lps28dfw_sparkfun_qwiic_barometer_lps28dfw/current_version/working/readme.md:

# sparkfun_qwiic_barometer_lps28dfw
 
## summary 
* id: sparkfun_sparkfun_qwiic_barometer_lps28dfw_sparkfun_qwiic_barometer_lps28dfw
* user: sparkfun
* name: sparkfun_qwiic_barometer_lps28dfw
* board: sparkfun_qwiic_barometer_lps28dfw
* repo: https://github.com/sparkfun/SparkFun_Qwiic_Barometer_LPS28DFW

* src_file_repo_sch: 
* src_file_repo_sch_link: https://github.com/sparkfun/SparkFun_Qwiic_Barometer_LPS28DFW/tree/main/
* full details link: https://github.com/oomlout/oomlout_oomp_project_bot_v_2/tree/main/projects/sparkfun_sparkfun_qwiic_barometer_lps28dfw_sparkfun_qwiic_barometer_lps28dfw/current_version/working

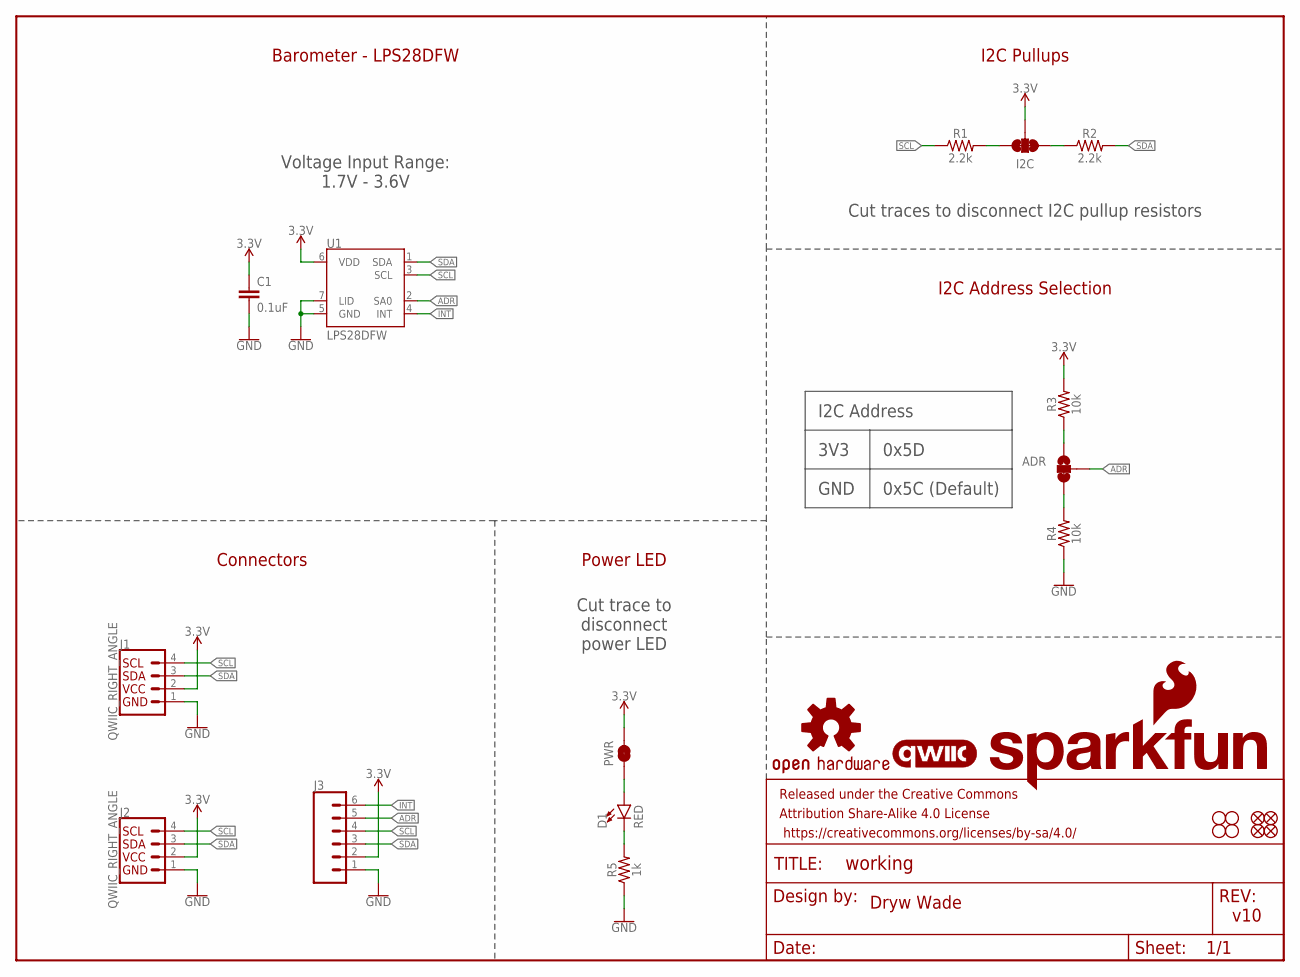
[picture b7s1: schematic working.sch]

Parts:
ADR: JUMPER-SMT_3_1-NC_TRACE_SILK; SMT-JUMPER_3_1-NC_TRACE_SILK
C1: 0.1uF; 0603
D1: RED; LED-0603
FD1, FD2, FD3, FD4: FIDUCIAL1X2; FIDUCIAL-1X2
FRAME1: FRAME-LETTER; CREATIVE_COMMONS
H1, H2, H3, H4: STAND-OFF
I2C: JUMPER-SMT_3_2-NC_TRACE_SILK; SMT-JUMPER_3_2-NC_TRACE_SILK
J1, J2: QWIIC_RIGHT_ANGLE; JST04_1MM_RA
J3: CONN_06NO_SILK_NO_POP; 1X06_NO_SILK
LOGO1: OSHW-LOGOS; OSHW-LOGO-S
LOGO2: QWIIC_LOGO_5MM; QWIIC_5MM
LOGO3: SFE_LOGO_NAME_FLAME.1_INCH; SFE_LOGO_NAME_FLAME_.1
PWR: JUMPER-SMT_2_NC_TRACE_SILK; SMT-JUMPER_2_NC_TRACE_SILK
R1, R2: 2.2k; 0603
R3, R4: 10k; 0603
R5: 1k; 0603
U1: LPS28DFW; CCLGA-7L

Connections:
3.3V: C1.1, I2C.2, J1.2, J2.2, J3.2, PWR.2, R3.2, U1.6 (VDD)
ADR: ADR.2, J3.5, U1.2 (SA0)
GND: C1.2, J1.1, J2.1, J3.1, R4.1, R5.1, U1.5 (GND), U1.7 (LID)
INT: J3.6, U1.4 (INT)
unnamed: D1.C, R5.2
unnamed: I2C.3, R1.2
unnamed: I2C.1, R2.1
unnamed: D1.A, PWR.1
unnamed: ADR.3, R4.2
unnamed: ADR.1, R3.1
SCL: J1.4, J2.4, J3.4, R1.1, U1.3 (SCL)
SDA: J1.3, J2.3, J3.3, R2.2, U1.1 (SDA)

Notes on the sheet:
Dryw Wade
v10
Barometer - LPS28DFW
I2C Pullups
I2C Address Selection
Connectors
Power LED
Cut traces to disconnect I2C pullup resistors
I2C Address
GND
3V3
0x5D
0x5C (Default)
Cut trace to disconnect power LED
Voltage Input Range: 1.7V - 3.6V
